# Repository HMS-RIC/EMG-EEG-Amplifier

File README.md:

# EMG/EEG-Amplifier
3 Channel instrumentation amplifier circuit using AD8221. 

**EMG:** 1 channel, fully differential. 3.2 Hz highpass and 100x gain.   
**EEG:** 2 channels use a common reference. 1.1 Hz highpass and 100x gain.  

Gain is set using a single 499 Ohm resistor per channel. 
Input bandwidth is set by RC network.

Black wire: GND  
Red wire: +5V  
White wire: -5V  
Blue wires (3): Outputs  

.asc file can be opened with LTspice to run the circuit simulation and plot frequency response and transient analysis

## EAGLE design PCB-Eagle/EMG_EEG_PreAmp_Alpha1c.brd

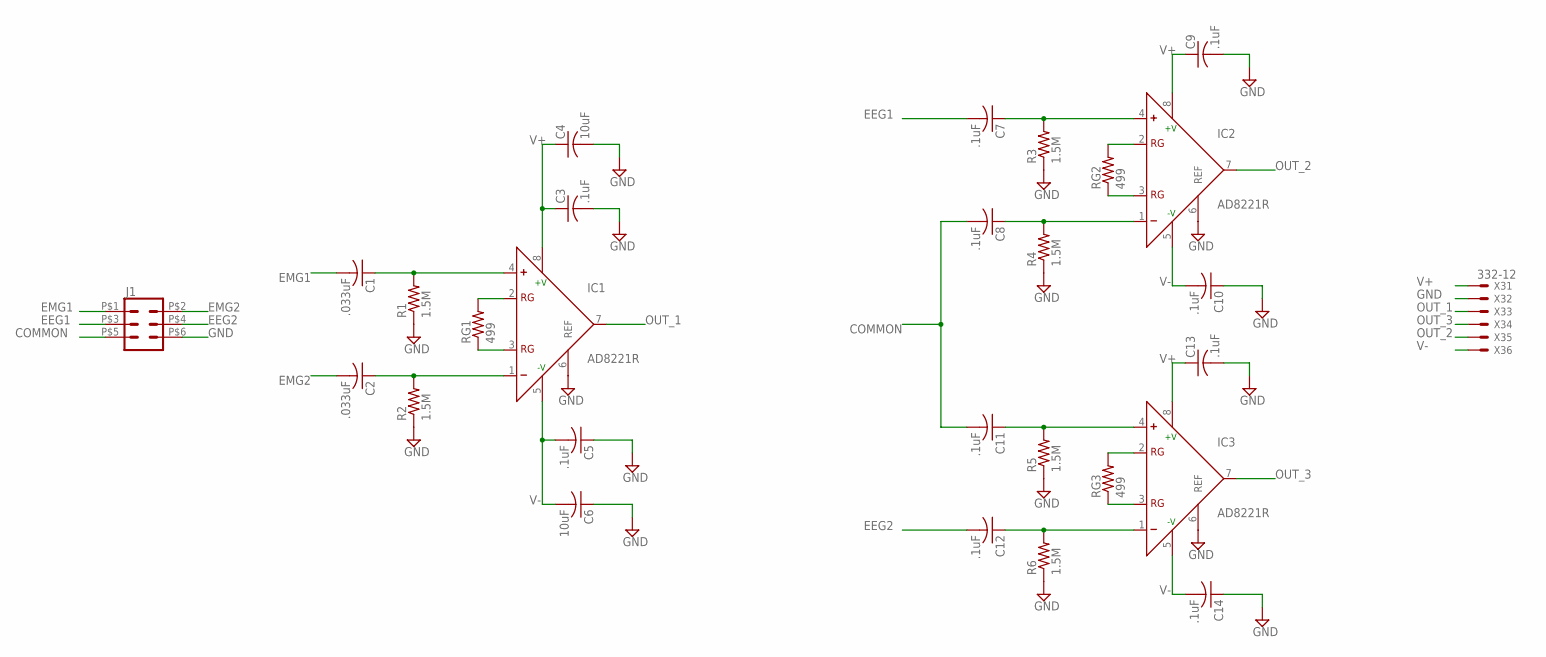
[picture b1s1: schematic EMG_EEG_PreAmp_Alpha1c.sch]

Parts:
C1, C2: .033uF; C0805K
C3, C5, C7, C8, C9, C10, C11, C12, C13, C14: .1uF; C0805K
C4, C6: 10uF; C0805K
IC1, IC2, IC3: AD8221R; SO8
J1: 2X3MILL-MAX; 2X3_MILL-MAX_853
R1, R2, R3, R4, R5, R6: 1.5M; R0805
RG1, RG2, RG3: 499; R0805
X3: 332-12; 1X6_WITH_STRAIN_RELIEF

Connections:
COMMON: C8.2, C11.2, J1.P$5 (5)
EEG1: C7.2, J1.P$3 (3)
EEG2: C12.2, J1.P$4 (4)
EMG1: C1.2, J1.P$1 (1)
EMG2: C2.2, J1.P$2 (2)
GND: C3.2, C4.2, C5.1, C6.1, C9.2, C10.1, C13.2, C14.1, IC1.6 (REF), IC2.6 (REF), IC3.6 (REF), J1.P$6 (6), R1.1, R2.1, R3.1, R4.1, R5.1, R6.1, X3.2
unnamed: IC1.3 (RG), RG1.1
unnamed: IC1.2 (RG), RG1.2
unnamed: C2.1, IC1.1 (-), R2.2
unnamed: C1.1, IC1.4 (+), R1.2
unnamed: IC2.3 (RG), RG2.1
unnamed: IC2.2 (RG), RG2.2
unnamed: C8.1, IC2.1 (-), R4.2
unnamed: C7.1, IC2.4 (+), R3.2
unnamed: IC3.3 (RG), RG3.1
unnamed: IC3.2 (RG), RG3.2
unnamed: C12.1, IC3.1 (-), R6.2
unnamed: C11.1, IC3.4 (+), R5.2
OUT_1: IC1.7 (OUT), X3.3
OUT_2: IC2.7 (OUT), X3.5
OUT_3: IC3.7 (OUT), X3.4
V+: C3.1, C4.1, C9.1, C13.1, IC1.8 (+V), IC2.8 (+V), IC3.8 (+V), X3.1
V-: C5.2, C6.2, C10.2, C14.2, IC1.5 (-V), IC2.5 (-V), IC3.5 (-V), X3.6

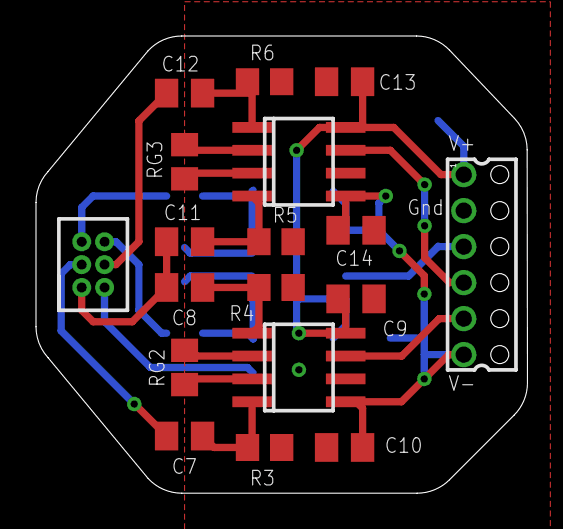
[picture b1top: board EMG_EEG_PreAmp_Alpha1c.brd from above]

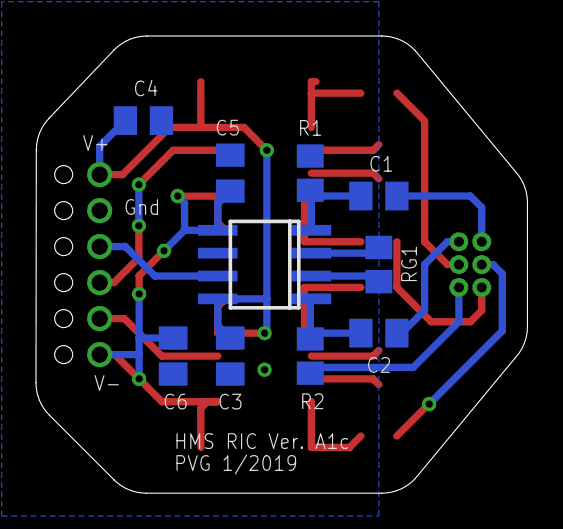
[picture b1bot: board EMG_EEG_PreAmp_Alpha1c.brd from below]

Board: 2 copper layers, 27.3 x 25.4 mm, 28 parts (10 on the bottom side), 23 nets.

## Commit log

2019-01-25 Create test
